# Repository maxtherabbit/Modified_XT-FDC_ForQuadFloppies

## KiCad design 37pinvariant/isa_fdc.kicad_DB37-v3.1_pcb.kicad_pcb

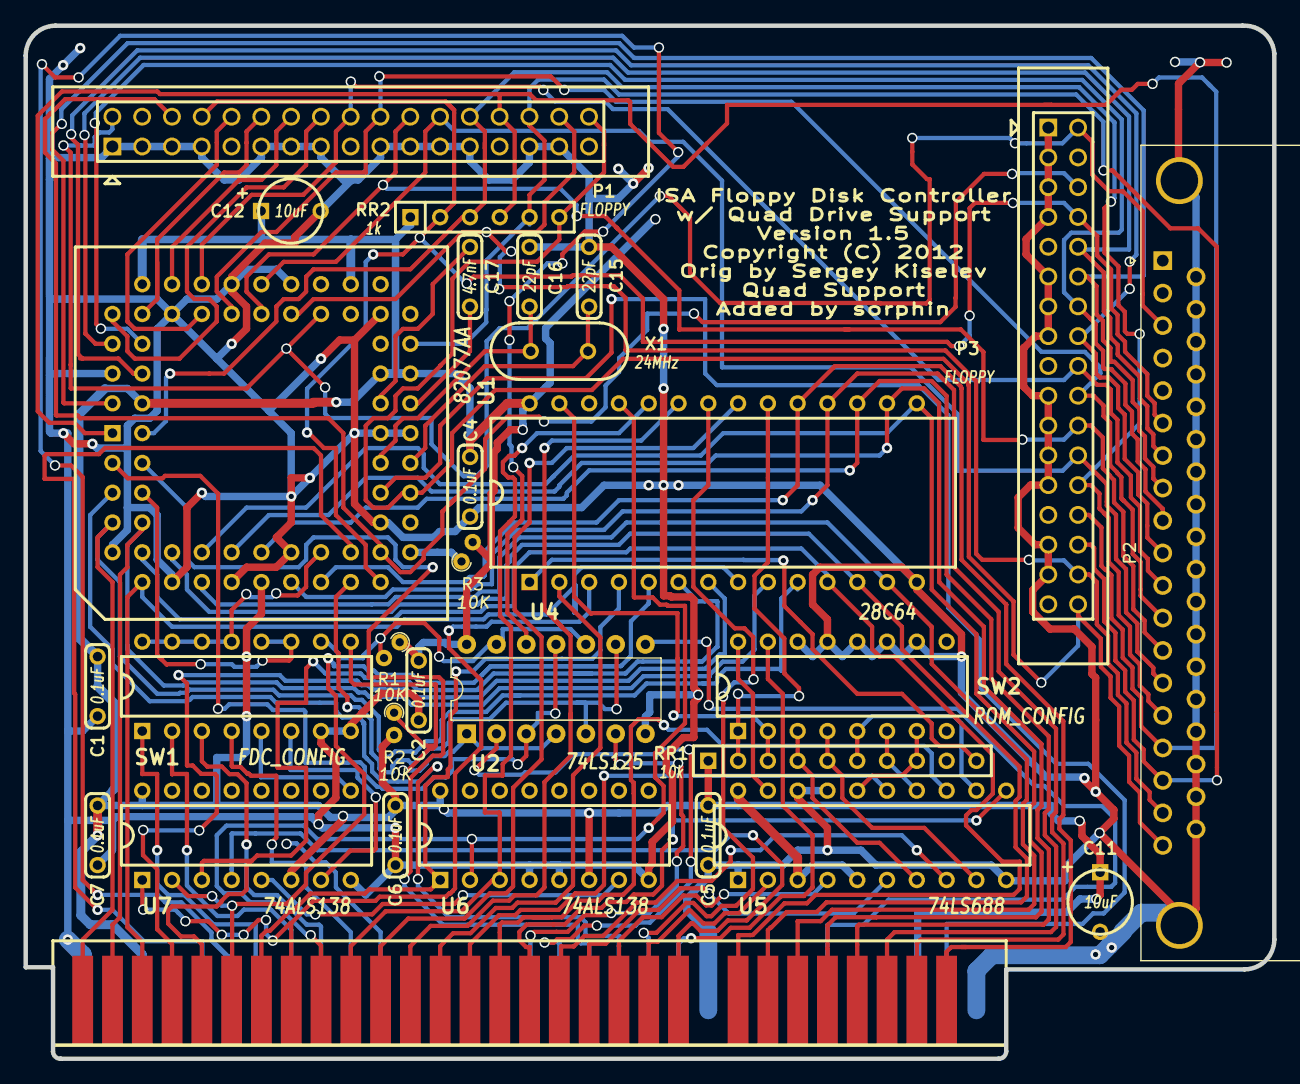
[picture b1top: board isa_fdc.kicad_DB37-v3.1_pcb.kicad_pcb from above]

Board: 2 copper layers, 106.5 x 88.1 mm, 29 parts (0 on the bottom side), 88 nets.

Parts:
BUS1: BUSPC_DEV; Conn_Bus_ISA8
C1, C2, C4, C5, C6, C7: 0.1uF; Cap_Cer_504
C11, C12: 10uF; Cap_Tant_504
C15, C16: 22pF; Cap_Cer_504
C17: 4.7nF; Cap_Cer_504
P1, P3: FLOPPY; Conn_Pin_Header_17x2_Shroud
P2: DB37 Female (External Floppy); DSUB-37_Female_Horizontal_P2.77x2.84mm_EdgePinOffset9.90mm_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
R1, R2, R3: 10K; R_Axial_DIN0204_L3.6mm_D1.6mm_P1.90mm_Vertical
RR1: 10k; Conn_SIL-10
RR2: 1k; Conn_SIL-6
SW1: FDC_CONFIG; DIP16_300
SW2: ROM_CONFIG; DIP16_300
U1: 82077AA; PLCC68_TH
U2: 74LS125; DIP-14_W7.62mm
U4: 28C64; DIP28_600
U5: 74LS688; DIP20_300
U6, U7: 74ALS138; DIP16_300
X1: 24MHz; Crystal_HC-49U_Vert

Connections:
/0x3F0: SW1.6, U7.7
/0x370: SW1.5, U7.9
/A0: BUS1.62, U1.7, U4.10
/A1: BUS1.61, U1.8, U4.9
/A2: BUS1.60, U1.10, U4.8
/A3: BUS1.59, U4.7
/A4: BUS1.58, U4.6, U7.3
/A5: BUS1.57, U4.5, U7.2
/A6: BUS1.56, U4.4, U6.1
/A7: BUS1.55, U4.3, U7.1
/A8: BUS1.54, U4.25, U6.2
/A9: BUS1.53, U4.24, U6.3
/A10: BUS1.52, U4.21
/A11: BUS1.51, U4.23
/A12: BUS1.50, U4.2
/A13: BUS1.49, U5.15
/A14: BUS1.48, U5.13
/A15: BUS1.47, U5.11
/A16: BUS1.46, U5.8
/A17: BUS1.45, U5.6
/A18: BUS1.44, U5.4
/A19: BUS1.43, U5.2
/AEN: BUS1.42, U7.4
/D0: BUS1.40, U1.11, U4.11
/D1: BUS1.39, U1.13, U4.12
/D2: BUS1.38, U1.14, U4.13
/D3: BUS1.37, U1.15, U4.15
/D4: BUS1.36, U1.17, U4.16
/D5: BUS1.35, U1.19, U4.17
/D6: BUS1.34, U1.20, U4.18
/D7: BUS1.33, U1.22, U4.19
/DENSL: P1.2, P2.3, P3.2, U1.49
/DIR: P1.18, P2.11, P3.18, U1.56
/DRATE0: P1.6, P3.6, U1.28
/DRQ: U1.24, U2.5, U2.9
/DRQ2: BUS1.6, U2.8
/DRQ3: BUS1.16, U2.6
/DS2: P2.9, P3.14, U1.64
/DS3: P2.8, P3.12, U1.67
/DSA: P1.14, U1.58
/DSB: P1.12, U1.62
/DSKCG: P1.34, P2.19, P3.34, RR2.6, U1.31
/FDC_IRQ: SW1.13, SW1.14, SW1.15, SW1.16, U1.23
/GT2: R1.2, SW1.10, U2.10, U2.13
/GT3: R2.1, SW1.9, U2.1, U2.4
/HDSEL: P1.32, P2.18, P3.32, U1.51
/IDENT: R3.1, U1.27
/INDEX: P1.8, P2.6, P3.8, RR2.2, U1.26
/IRQ3: BUS1.25, SW1.1
/IRQ4: BUS1.24, SW1.2
/IRQ5: BUS1.23, SW1.3
/IRQ6: BUS1.22, SW1.4
/ME2: P2.7, P3.10, U1.63
/ME3: P2.10, P3.16, U1.66
/MEA: P1.10, U1.57
/MEB: P1.16, U1.61
/RDATA: P1.30, P2.17, P3.30, RR2.5, U1.41
/RDY/~BUSY: RR1.10, U4.1
/RESETDRV: BUS1.2, U1.32
/STEP: P1.20, P2.12, P3.20, U1.55
/TC: BUS1.27, U1.25
/TRK00: P1.26, P2.15, P3.26, RR2.3, U1.2
/WDATA: P1.22, P2.13, P3.22, U1.53
/WE: P1.24, P2.14, P3.24, U1.52
/WP: P1.28, P2.16, P3.28, RR2.4, U1.1
/~DACK: U1.3, U2.3, U2.11
/~DACK2: BUS1.26, U2.12
/~DACK3: BUS1.15, U2.2
/~FDC_CS: SW1.11, SW1.12, U1.6
/~IOR: BUS1.14, U1.4
/~IOW: BUS1.13, U1.5
/~MEMR: BUS1.12, U4.22
/~MEMW: BUS1.11, SW2.15
/~ROMW: RR1.3, SW2.2, U4.27
/~ROM_CS: RR1.2, SW2.1, U4.20
/~ROM_CS_IN: SW2.16, U5.19
GND: BUS1.1, BUS1.10, BUS1.31, C1.2, C2.2, C4.2, C5.2, C6.2, C7.2, C11.2, C12.2, C15.2, C16.2, P1.1, P1.3, P1.5, P1.7, P1.11, P1.13, P1.15, P1.19, P1.21, P1.23, P1.25, P1.29, P1.31, P2.0, P2.20, P2.21, P2.22, P2.23, P2.24, P2.25, P2.26, P2.27, P2.28, P2.29, P2.30, P2.31, P2.32, P2.33, P2.34, P2.35, P2.36, P2.37, P3.1, P3.3, P3.5, P3.7, P3.11, P3.13, P3.15, P3.19, P3.21, P3.23, P3.25, P3.29, P3.31, SW1.7, SW1.8, SW2.10, SW2.11, SW2.12, SW2.13, SW2.14, U1.9, U1.12, U1.16, U1.21, U1.30, U1.35, U1.36, U1.45, U1.50, U1.54, U1.59, U1.65, U2.7, U4.14, U5.1, U5.10, U5.17, U5.18, U6.4, U6.5, U6.8, U7.8
unnamed: C15.1, U1.33, X1.1
unnamed: C16.1, U1.34, X1.2
unnamed: C17.1, U1.38
unnamed: C17.2, U1.37
unnamed: RR1.4, SW2.3, U5.7
unnamed: RR1.5, SW2.4, U5.9
unnamed: RR1.6, SW2.5, U5.12
unnamed: RR1.7, SW2.6, U5.14
unnamed: RR1.8, SW2.7, U5.16
unnamed: U6.7, U7.5
VCC: BUS1.3, BUS1.29, C1.1, C2.1, C4.1, C5.1, C6.1, C7.1, C11.1, C12.1, R1.1, R2.2, R3.2, RR1.1, RR2.1, U1.18, U1.39, U1.40, U1.46, U1.60, U1.68, U2.14, U4.28, U5.3, U5.5, U5.20, U6.6, U6.16, U7.6, U7.16

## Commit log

2020-08-01 Create placeholder
2020-08-02 Create stubfile
2020-08-02 Create stub
2020-08-03 Rename 37pinvarient/isa_fdc.kicad_DB37-v3.1_pcb.kicad_pcb to 37pinvariant/isa_fdc.kicad_DB37-v3.1_pcb.kicad_pcb
2020-08-03 Rename varient to variant
2020-08-06 adjust DC-37 fitment and lower ISA contact fingers

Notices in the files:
37pinvariant/isa_fdc.kicad_DB37-v3.1_pcb.kicad_pcb:
Copyright (C) 2012
